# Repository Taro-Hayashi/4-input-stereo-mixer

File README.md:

# 4入力ステレオミキサー ビルドガイド
- [ご注意](#ご注意)
- [部品リスト](#部品リスト)
- [組み立て](#組み立て)
- [おまけ](#おまけ)
- [ライセンス](#ライセンス)

## ご注意
- Type-A to Type-Cケーブルでのみ給電できます。
- ボリューム調整機能はありません。
- マイクには対応していません。
- 入力端子同士の間隔は1.2cmです。

## 部品リスト
  
|Ref|部品名|数|
|-|-|-|
||メインボード||
||アクリルプレート||
||0.01mm両面テープ||
||5mmM2ねじ|8|
||3x8mmスペーサー|4|
|U1|丸ピンICソケット 14P|1|
||オペアンプ LME49740NA|1|
|MAU108|レギュレーター MAU108|1|
|REG1|レギュレーター NJM7805FA|1|
|USB1|Type-Cコネクタ電源供給用|1|
|TRRS1-5|MJ-4PP-9|5|
|R1-10|47kΩ|10|
|R11-16|10kΩ|6|
|R11-16|10kΩ|6|
|R17,18|51Ω|2|
|R19,20|100kΩ|2|
|R_LED|200Ω|1|
|C1,2|0.1uF フィルムコンデンサー|2|
|C3,4|100uF 電源用電解コンデンサー|2|
|C5-8|100uF OS-CON|4|
|C9-16|1uF オーディオ用無極性コンデンサー|8|
|C17,18|4.7uF オーディオ用無極性コンデンサー|2|
|D1|1N4007|1|
|L1|4.7uH|1|
|LED1|3mmLED 3V 20mA|1|
||キースイッチ|1|
||キーキャップ|1|
||スイッチソケット|1|
||ゴム足|4|

### 工具（必要に応じて準備してください）
|工具名||
|-|-|
|はんだ付け用工具一式||
|精密ドライバー||
|ニッパー|抵抗等の足を切ります。|
|ラジオペンチ|レギュレーターの足を曲げます。ニッパーでも可能です。|
|アクリサンデー ポリケアF70|指紋を拭いたりホコリを付きにくくできます。|
|アクリサンデー 研磨剤|側面を磨いてツルツルにしたり、細かい傷を消すことができます。|
|アクリル接着剤|両面テープの代わりに使うと強固に接着できます。|

## 組み立て
電子部品は番号通りに部品をはんだ付けするだけなのでビルドガイドを見なくても制作可能です。高さが低い順番にはんだ付けする様子を写真で紹介しています。  

Type-Cコネクタはマスキングテープなどで固定するとはんだ付けしやすいです。

OS-CONには極性があります。足が長い方が+（白い側）です。  
  
レギュレーターの足をラジオペンチ等で曲げます。

コイルや抵抗は写真のように足を曲げて縦に取り付けます。

フィルムコンデンサーには極性がありません。
  
電源用電解コンデンサーには極性があります。
  
オーディオ用コンデンサーには極性がありません。

すべてのパーツをはんだ付けしたらオペアンプを差し込んで動作を確認しましょう。

アクリルケースを組み立てます。スペーサー4つをネジで取り付けます。

アクリルプレートから保護フィルムを剥がしのせていきます。順番は写真を参考にしてください。

ネジは締めきらず、微調整できるようにしておくと側面を綺麗に揃えやすいです。  
  
裏返して片面を剥がした両面テープを貼ります。皮脂が付いていると剥がれやすくなるので気をつけてください。  

両面テープをはがし、側面のカーブを合わせて貼り付けます。
  
残りのプレートも同じように貼り付けます。

好みのキースイッチを差し込んで、ゴム足とキーキャップを付けたら完成です。 

## おまけ
### LEDを光らせる
キースイッチによってはLEDを取り付ける穴が開いていないことがあります。また、LEDをはんだ付けするとキースイッチを外せなくなります。  
裏面のネジを外してプレートを取り除き、キースイッチの上からLEDを差します。写真と同じように、長い方の足が四角のパッドから出るようにしてください。  

はんだ付けして足を切り、プレートを戻します。
  
USBを繋いでスイッチを押すとLEDが発光します。

### ノイズ対策
ジリジリしたノイズが乗っている場合、グラウンドループアイソレーターを使うことで解決することがあります。
おまけの基板に別売りのTRRSジャック（[MJ-4PP-9](https://akizukidenshi.com/catalog/g/gC-06070/)）とトランス（[AT129](https://akizukidenshi.com/catalog/g/gP-14522/)）をはんだ付けすると作ることができます。

検索すると市販のものもたくさん出てくるので好きなものを使ってください。

#### KiCad ファイル
- [KiCad](KiCad)

#### ガーバー
- [gerber](gerber)

## 販売ページ
- [BOOTH](https://tarohayashi.booth.pm/items/4152188)

## ライセンス
KiCadファイル（`KiCad/`）とガーバーファイル（`gerber/`）は、CC0 1.0 Universalでパブリックドメインに提供します。

これらのファイルは、表記なしで利用、改変、製造、配布、販売できます。

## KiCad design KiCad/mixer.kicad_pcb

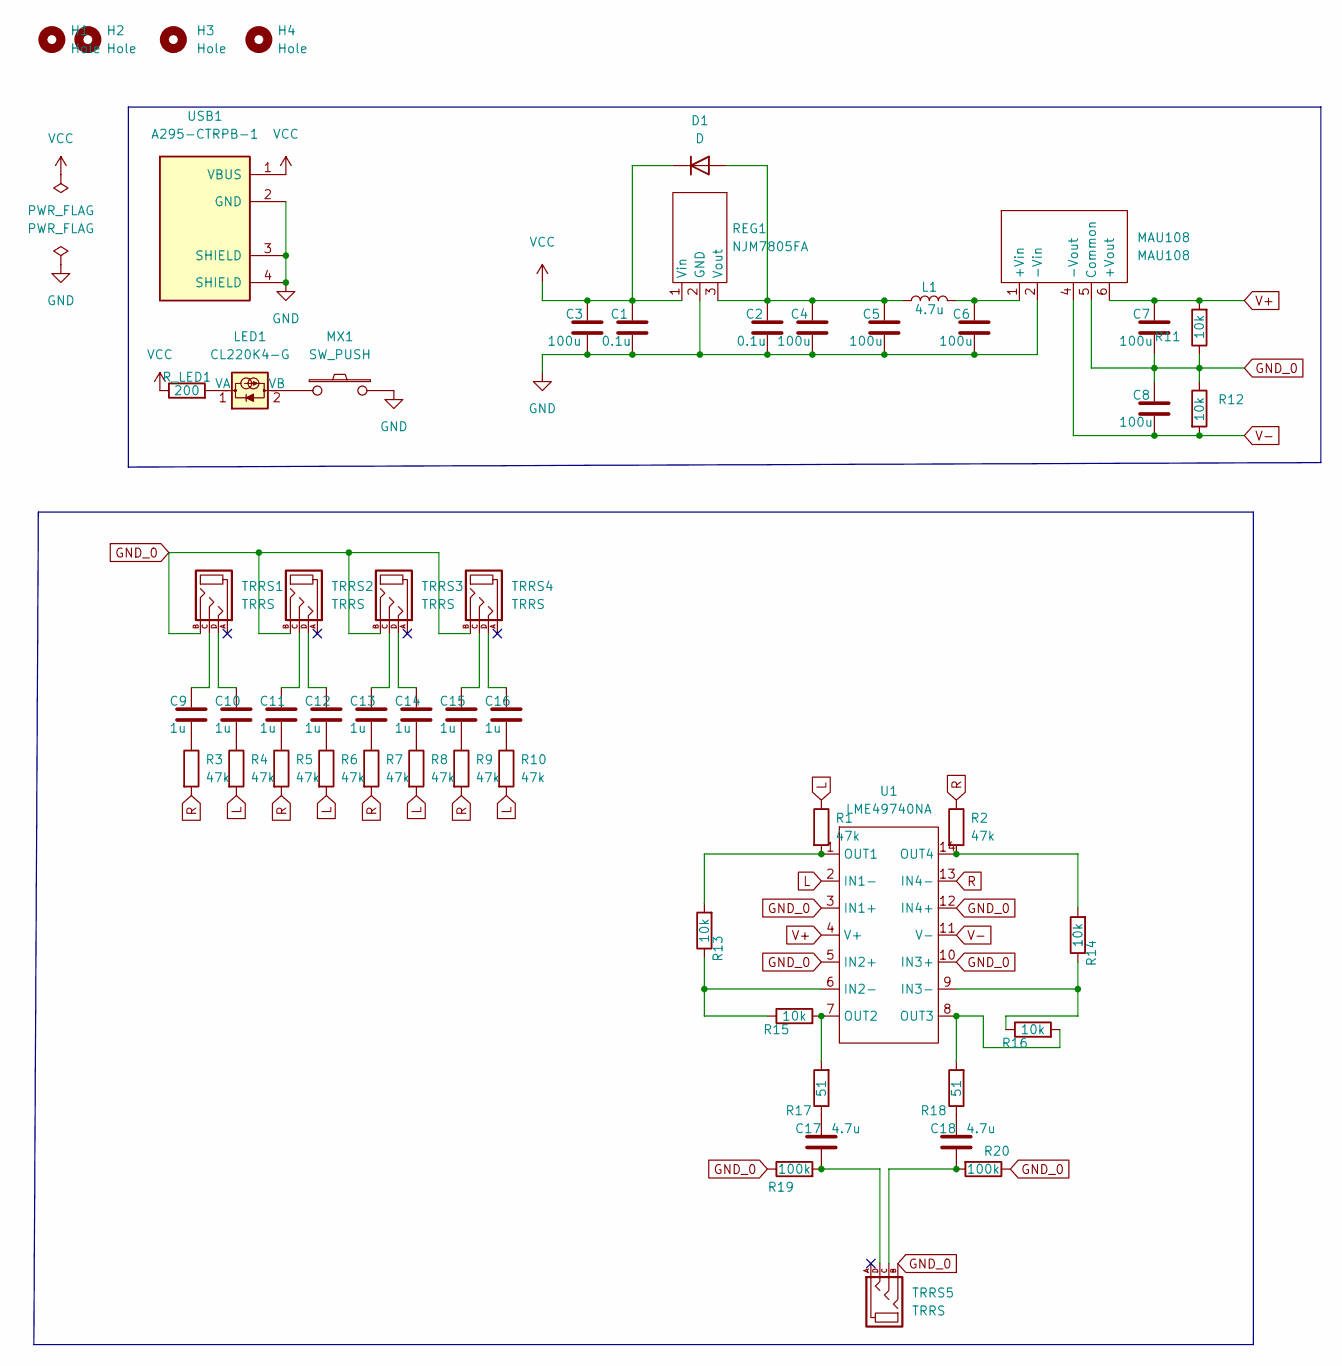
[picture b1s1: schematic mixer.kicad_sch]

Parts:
C1, C2: 0.1u; C_Disc_D9.0mm_W5.0mm_P5.00mm
C3, C4, C5, C6, C7, C8: 100u; CP_Radial_D6.3mm_P2.50mm
C9, C10, C11, C12, C13, C14, C15, C16: 1u; C_Radial_D5.0mm_H11.0mm_P2.00mm
C17, C18: 4.7u; C_Radial_D5.0mm_H11.0mm_P2.00mm
D1: D; D_A-405_P7.62mm_Horizontal
H1, H2, H3, H4: Hole; Hole_2.2mm_M2
L1: 4.7u; L_Axial_L7.0mm_D3.3mm_P2.54mm_Vertical_Fastron_MICC
LED1: CL220K4-G; LED_D3.0mm
MAU108: MAU108; Converter_DCDC_Murata_NMAxxxxSC_THT
MX1: SW_PUSH; MXOnly-1U-Hotswap
R1, R2, R3, R4, R5, R6, R7, R8, R9, R10: 47k; R_Axial_DIN0207_L6.3mm_D2.5mm_P2.54mm_Vertical
R11, R12, R13, R14, R15, R16: 10k; R_Axial_DIN0207_L6.3mm_D2.5mm_P2.54mm_Vertical
R17, R18: 51; R_Axial_DIN0207_L6.3mm_D2.5mm_P2.54mm_Vertical
R19, R20: 100k; R_Axial_DIN0207_L6.3mm_D2.5mm_P2.54mm_Vertical
REG1: NJM7805FA; TO-220F-3_Horizontal_TabUp
R_LED1: 200; R_Axial_DIN0207_L6.3mm_D2.5mm_P2.54mm_Vertical
TRRS1, TRRS2, TRRS3, TRRS4, TRRS5: TRRS
U1: LME49740NA; DIP-14_W7.62mm_Socket
USB1: A295-CTRPB-1

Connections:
GND: C1.2, C2.2, C3.2, C4.2, C5.2, C6.2, MAU108.2 (-Vin), MX1.2, REG1.2 (GND), USB1.2 (GND), USB1.3 (SHIELD), USB1.4 (SHIELD)
GND_0: C7.2, C8.1, MAU108.5 (Common), R11.1, R12.1, R19.1, R20.1, TRRS1.B, TRRS2.B, TRRS3.B, TRRS4.B, TRRS5.B, U1.3 (IN1+), U1.5 (IN2+), U1.10 (IN3+), U1.12 (IN4+)
L: R1.1, R4.2, R6.2, R8.2, R10.2, U1.2 (IN1-)
unnamed: C2.1, C4.1, C5.1, D1.2 (A), L1.1, REG1.3 (Vout)
unnamed: C6.1, L1.2, MAU108.1 (+Vin)
unnamed: C9.1, TRRS1.C
unnamed: C9.2, R3.1
unnamed: C10.1, TRRS1.D
unnamed: C10.2, R4.1
unnamed: C11.1, TRRS2.C
unnamed: C11.2, R5.1
unnamed: C12.1, TRRS2.D
unnamed: C12.2, R6.1
unnamed: C13.1, TRRS3.C
unnamed: C13.2, R7.1
unnamed: C14.1, TRRS3.D
unnamed: C14.2, R8.1
unnamed: C15.1, TRRS4.C
unnamed: C15.2, R9.1
unnamed: C16.1, TRRS4.D
unnamed: C16.2, R10.1
unnamed: C17.1, R17.1
unnamed: C17.2, R19.2, TRRS5.D
unnamed: C18.1, R18.1
unnamed: C18.2, R20.2, TRRS5.C
unnamed: LED1.2 (VB), MX1.1
unnamed: R1.2, R13.2, U1.1 (OUT1)
unnamed: R13.1, R15.1, U1.6 (IN2-)
unnamed: R14.1, R16.1, U1.9 (IN3-)
unnamed: R2.2, R14.2, U1.14 (OUT4)
unnamed: R15.2, R17.2, U1.7 (OUT2)
unnamed: R16.2, R18.2, U1.8 (OUT3)
unnamed: LED1.1 (VA), R_LED1.2
R: R2.1, R3.2, R5.2, R7.2, R9.2, U1.13 (IN4-)
V+: C7.1, MAU108.6 (+Vout), R11.2, U1.4 (V+)
V-: C8.2, MAU108.4 (-Vout), R12.2, U1.11 (V-)
VCC: C1.1, C3.1, D1.1 (K), REG1.1 (Vin), R_LED1.1, USB1.1 (VBUS)

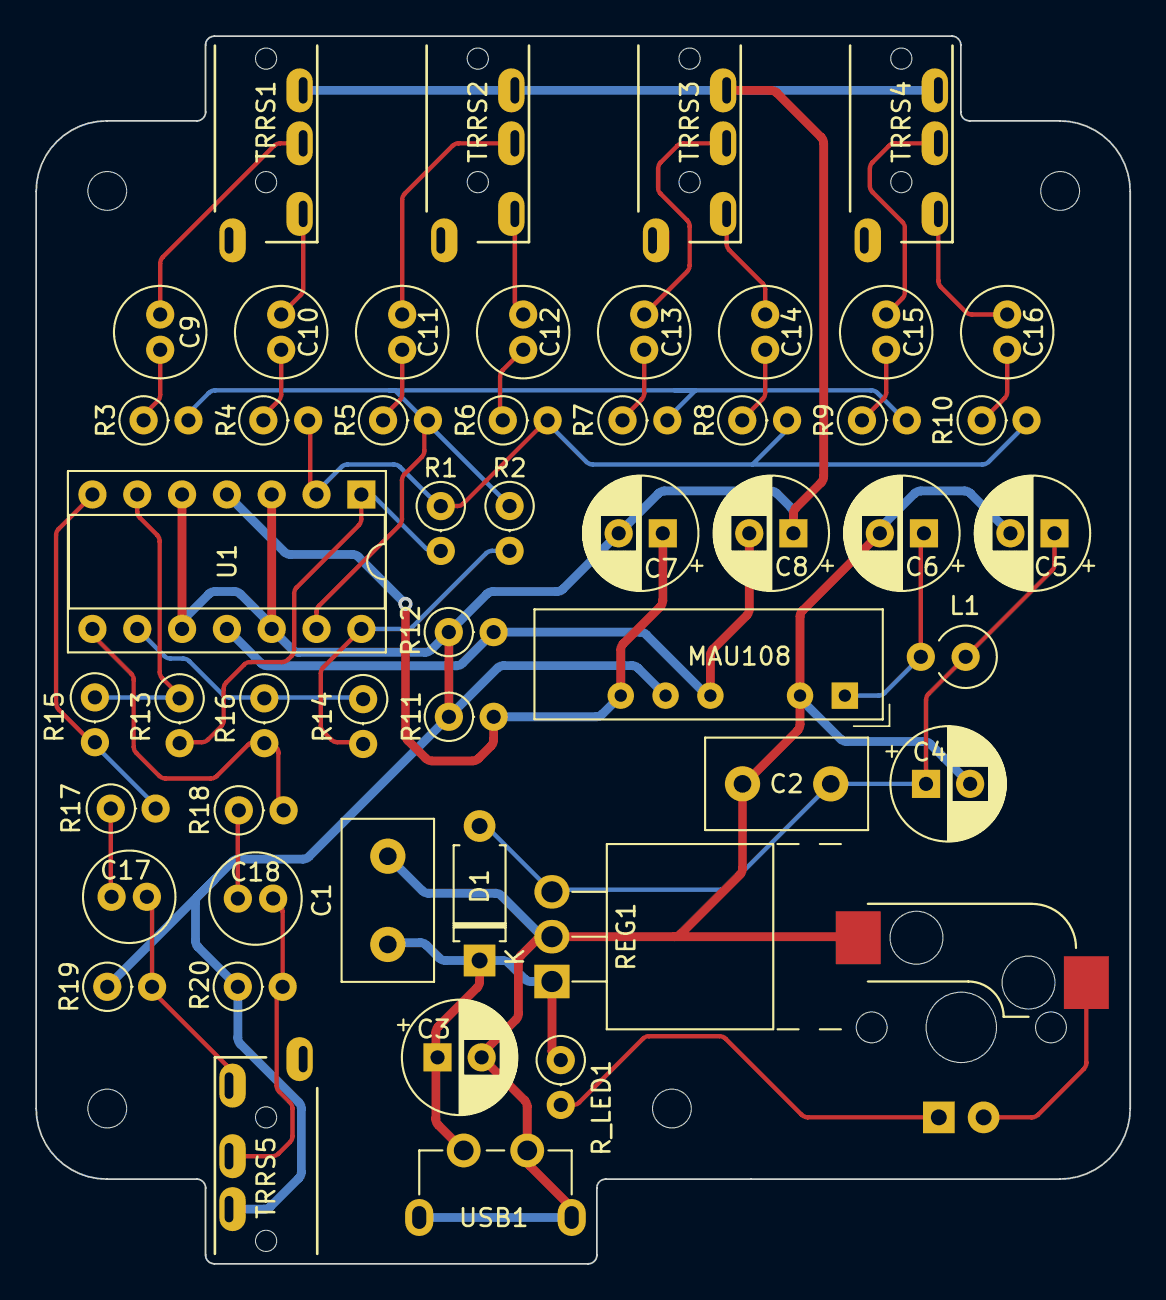
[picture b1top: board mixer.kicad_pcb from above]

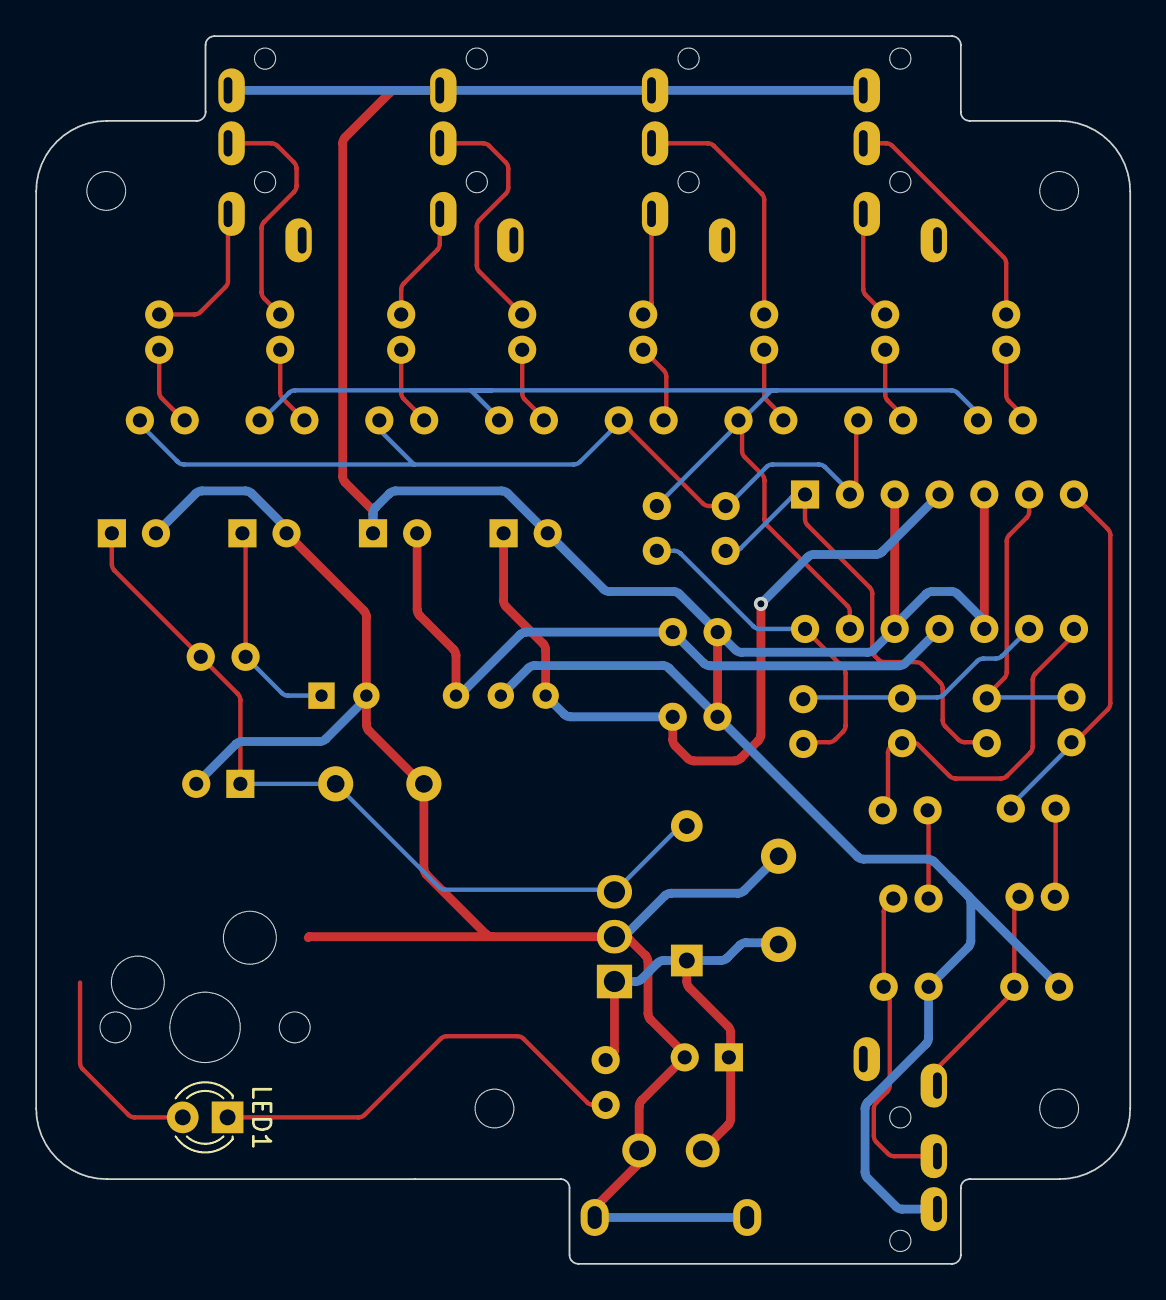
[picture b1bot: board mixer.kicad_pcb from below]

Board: 2 copper layers, 62.0 x 69.6 mm, 56 parts (2 on the bottom side), 37 nets.

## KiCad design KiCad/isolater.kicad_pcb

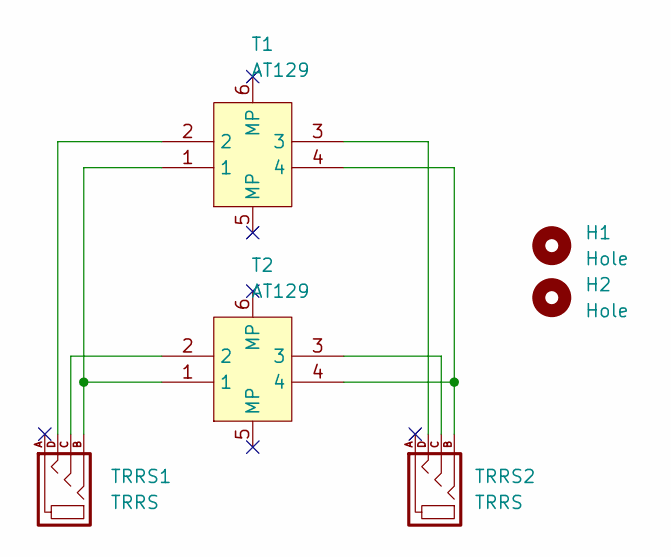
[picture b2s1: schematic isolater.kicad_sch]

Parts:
H1, H2: Hole; Hole_2.2mm_M2
T1, T2: AT129
TRRS1, TRRS2: TRRS

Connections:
unnamed: T1.1, T2.1, TRRS1.B
unnamed: T1.2, TRRS1.D
unnamed: T1.3, TRRS2.D
unnamed: T1.4, T2.4, TRRS2.B
unnamed: T2.2, TRRS1.C
unnamed: T2.3, TRRS2.C

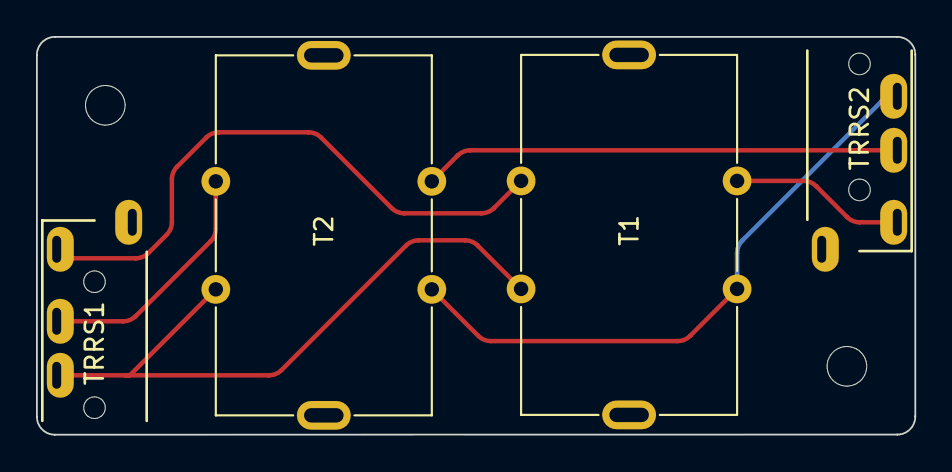
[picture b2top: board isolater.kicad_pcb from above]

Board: 2 copper layers, 48.8 x 22.1 mm, 6 parts (0 on the bottom side), 6 nets.

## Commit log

2026-05-23 License hardware files under CC0
